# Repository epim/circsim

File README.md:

# circsim

**Simulate and audit any routed KiCad board.** circsim is a desktop app (Windows / macOS / Linux) that opens a routed KiCad board (`.kicad_pcb`), rebuilds the circuit from the copper, renders it in 3D, and runs an interactive SPICE bench on it: apply power, turn a knob, probe nets on the physical board. A read-only Board Critic audits the layout for fabrication risks. You get both before you pay for fabrication.

Open the board and press Energize. You do not assign `Sim.*` fields first, and the bundled model library matches parts by part number, value, and footprint, flagging the ones it cannot match instead of guessing. circsim is fully offline, MIT-licensed, and **never modifies your design files.**

Documentation: **[epim.github.io/circsim](https://epim.github.io/circsim/)**. It has the install guide, the First Light tutorial, task how-tos, and the full reference.
Download: **[latest release](https://github.com/epim/circsim/releases/latest)** (Windows `.exe`, macOS `.dmg` x2, Linux `.AppImage` / `.deb`).

More screenshots, and what circsim reads out of sixteen KiCad-written boards from KiCad 6 through 10, are in the [gallery](https://epim.github.io/circsim/gallery).

## What it does

- **Starts from the routed board.** Net connectivity comes straight out of the `.kicad_pcb`, KiCad 6 to 10. The board can come from your own KiCad project, a contractor, or an autorouter such as [Quilter](https://quilter.ai) that returns a KiCad board; circsim has no Quilter-specific code. The [supported files](https://epim.github.io/circsim/reference/file-formats#kicad-version-support) page lists the KiCad-written boards behind the version range, including the one it rejects.
- **The schematic is an optional input.** Keep the `.kicad_sch` next to the board with the same name and circsim attaches it on open. Its `Sim.*` fields are the first model source and its pin names settle diode and LED polarity. Only the root sheet is read, so parts on hierarchical sub-sheets get neither. A BOM CSV pins down exact parts.
- **A real bench.** Clip a DC supply, function generator, potentiometer, logic input, and voltage/current probes onto the board by drawing leads from front-panel jacks to the copper. Turn a knob and the simulation re-solves live.
- **A read-only Board Critic on the layout.** It audits the board circsim did *not* design for floating nets, clearance, decoupling distance, loop area, IR-drop, ampacity, and thermal risk, and never edits your files. The simulation itself treats each net as one ideal node, so copper resistance appears in the Critic's estimates and not in the simulated voltages.
- **Honest about what it knows.** Behavioral vs. primitive models, stubbed ICs, MCUs as interactive-pin panels (firmware doesn't run), convergence fallbacks, and fidelity limits are always visible. See [what circsim can and can't tell you](https://epim.github.io/circsim/concepts/fidelity). The same page ships inside the app.

Powered by [ngspice](https://ngspice.sourceforge.io/) 46, bundled per platform and run crash-isolated in a separate process. Nothing to install; no network calls, ever, and the app enforces it by cancelling any request that is not a local file.

## Develop

```sh
npm install
npm run fetch:ngspice   # download the bundled SPICE engine for your platform
npm run dev             # run the app in dev mode
npm test                # vitest unit + integration suite
npm run typecheck       # tsconfig.node.json + tsconfig.web.json (what CI runs)
npm run test:e2e        # Playwright E2E (requires npm run build first)
npm run build           # build the app
npm run package         # produce installers for the current platform
```

Architecture: Electron + TypeScript + React (panels) + imperative Three.js/WebGL2 (3D viewport) + zustand (state). The framework-free `src/core/` layer (KiCad parsing, netlist extraction, model resolution, SPICE-deck generation, the Board Critic) is fully unit-tested without Electron. See the [architecture reference](https://epim.github.io/circsim/reference/architecture).

## Documentation source

The docs site is a VitePress project under [`website/`](website/), deployed to GitHub Pages by [`.github/workflows/docs.yml`](.github/workflows/docs.yml) on every push touching `website/`. To work on it:

```sh
cd website && npm install && npm run docs:dev
```

The page the app opens from its About dialog and fidelity banner is rendered from `website/docs/concepts/fidelity.md`. After editing that page, run `npm run docs:fidelity` and commit the regenerated `docs/what-circsim-can-tell-you.html`; a unit test fails when the two drift.

## License

MIT. circsim bundles ngspice (BSD-style) and an in-house SPICE model library written from datasheet parameters; it never bundles vendor SPICE models or KiCad's share-alike 3D assets. See [`docs/licensing.md`](docs/licensing.md) and the in-app **About** dialog for full provenance.

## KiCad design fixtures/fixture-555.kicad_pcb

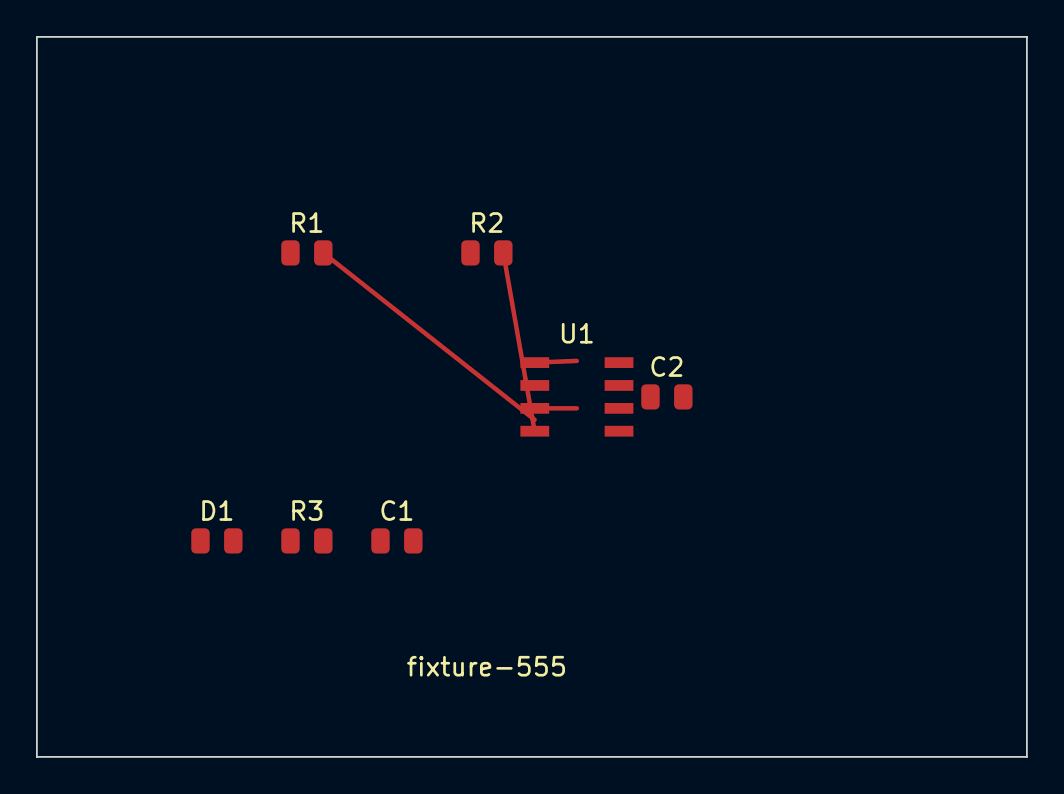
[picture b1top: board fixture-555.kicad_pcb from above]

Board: 2 copper layers, 55.0 x 40.0 mm, 7 parts (0 on the bottom side), 7 nets.

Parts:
C1: 10u; C_0805_2012Metric
C2: 100n; C_0805_2012Metric
D1: LED; LED_0805_2012Metric
R1: 10k; R_0805_2012Metric
R2: 47k; R_0805_2012Metric
R3: 330; R_0805_2012Metric
U1: NE555; SOIC-8_3.9x4.9mm_P1.27mm

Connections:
CTRL: C2.1, U1.5
DISCH: R1.2, R2.1, U1.7
GND: C1.2, C2.2, D1.2, U1.1
LED_A: D1.1, R3.2
OUT: R3.1, U1.3
THRES: C1.1, R2.2, U1.2, U1.6
VCC: R1.1, U1.4, U1.8

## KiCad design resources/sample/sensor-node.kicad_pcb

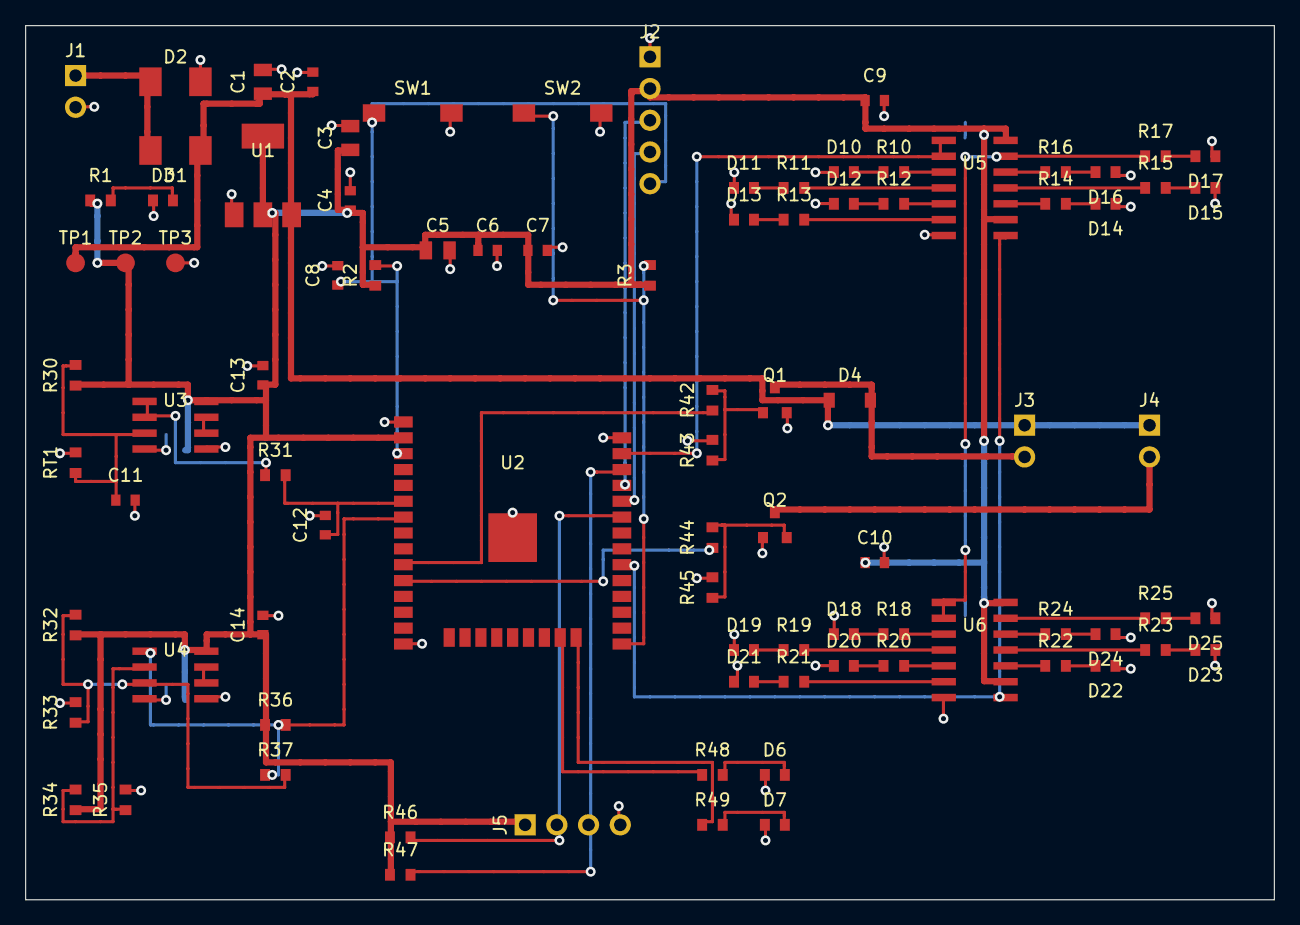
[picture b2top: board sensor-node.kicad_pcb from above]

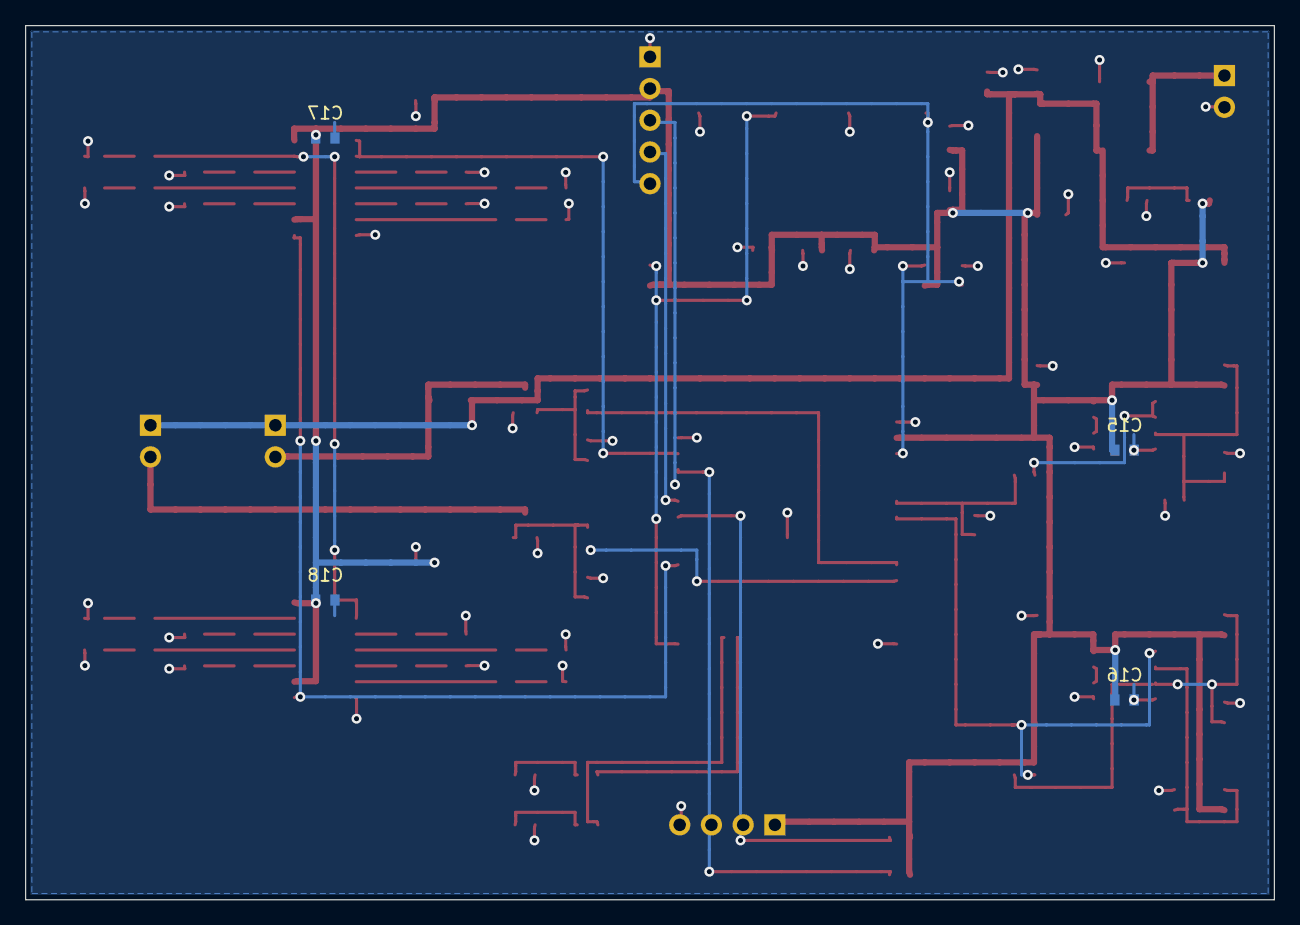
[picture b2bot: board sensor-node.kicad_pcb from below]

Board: 2 copper layers, 100.0 x 70.0 mm, 94 parts (4 on the bottom side), 63 nets.

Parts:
C1, C5: 10u; C_0805_2012Metric
C2, C4, C6, C7, C9, C10, C11, C13, C14, C15, C16, C17, C18: 100n; C_0603_1608Metric
C3: 22u; C_0805_2012Metric
C8: 1u; C_0603_1608Metric
C12: 10n; C_0603_1608Metric
D1: SS14; D_SMA
D2: SMAJ24A; D_SMA
D3, D6, D7, D10, D11, D12, D13, D14, D15, D16, D17, D18, D19, D20, D21, D22, D23, D24, D25: LED; LED_0603_1608Metric
D4: 1N4148W; D_SOD-123
J1, J3, J4: Conn_01x02; PinHeader_1x02_P2.54mm_Vertical
J2: Conn_01x05; PinHeader_1x05_P2.54mm_Vertical
J5: Conn_01x04; PinHeader_1x04_P2.54mm_Vertical
Q1: 2N7002; SOT-23
Q2: 2N3904; SOT-23
R1, R10, R11, R12, R13, R14, R15, R16, R17, R18, R19, R20, R21, R22, R23, R24, R25: 330; R_0603_1608Metric
R2, R3, R30, R32, R33, R36, R45: 10k; R_0603_1608Metric
R31, R44, R48, R49: 1k; R_0603_1608Metric
R34, R35: 47k; R_0603_1608Metric
R37: 1M; R_0603_1608Metric
R42: 220; R_0603_1608Metric
R43: 100k; R_0603_1608Metric
R46, R47: 4.7k; R_0603_1608Metric
RT1: 10k; R_0603_1608Metric
SW1, SW2: SW_Push; SW_SPST_PTS645
TP1, TP2, TP3: TestPoint; TestPoint_Pad_D1.5mm
U1: AMS1117-3.3; SOT-223
U2: ESP32-WROOM-32
U3: LM358; SOIC-8_3.9x4.9mm_P1.27mm
U4: LM393; SOIC-8_3.9x4.9mm_P1.27mm
U5, U6: 74HC164; SOIC-14_3.9x8.7mm_P1.27mm

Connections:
+3V3: C3.1, C4.1, C5.1, C6.1, C7.1, C9.1, C10.1, C13.1, C14.1, C15.1, C16.1, C17.1, C18.1, J2.2, J5.1, R1.1, R2.1, R3.1, R30.1, R32.1, R34.1, R36.1, R46.1, R47.1, TP2.1, U1.2, U1.4, U2.2, U3.8, U4.8, U5.9, U5.14, U6.9, U6.14
+5V: C1.1, C2.1, D1.1, D4.1, J3.1, J4.1, TP1.1, U1.3
EN: C8.1, J2.5, R2.2, SW1.1, U2.3
FAN_G: Q1.1, R42.2, R43.1
FAN_G_IN: R42.1, U2.10
FAN_NEG: D4.2, J3.2, Q1.3
GND: C1.2, C2.2, C3.2, C4.2, C5.2, C6.2, C7.2, C8.2, C9.2, C10.2, C11.2, C12.2, C13.2, C14.2, C15.2, C16.2, C17.2, C18.2, D2.2, D3.1, D6.1, D7.1, D10.1, D11.1, D12.1, D13.1, D14.1, D15.1, D16.1, D17.1, D18.1, D19.1, D20.1, D21.1, D22.1, D23.1, D24.1, D25.1, J1.2, J2.1, J5.4, Q1.2, Q2.1, R33.2, R35.2, R43.2, R45.2, RT1.2, SW1.2, SW2.2, TP3.1, U1.1, U2.1, U2.15, U2.38, U2.39, U3.4, U3.5, U4.4, U4.5, U5.7, U6.7
IO0: R3.2, SW2.1, U2.25
LA1: D10.2, R10.1
LA2: D11.2, R11.1
LA3: D12.2, R12.1
LA4: D13.2, R13.1
LA5: D14.2, R14.2
LA6: D15.2, R15.2
LA7: D16.2, R16.2
LA8: D17.2, R17.2
LA9: D18.2, R18.1
LA10: D19.2, R19.1
LA11: D20.2, R20.1
LA12: D21.2, R21.1
LA13: D22.2, R22.2
LA14: D23.2, R23.2
LA15: D24.2, R24.2
LA16: D25.2, R25.2
LDR_SENSE: R32.2, R33.1, R37.2, U4.3
LED_STATUS1: R48.1, U2.23
LED_STATUS2: R49.1, U2.24
LIGHT_ADC: R36.2, R37.1, U2.7, U4.1
LIGHT_REF: R34.2, R35.1, U4.2
NTC_SENSE: C11.1, R30.2, RT1.1, U3.3
PWR_LED_A: D3.2, R1.2
Q1: R10.2, U5.3
Q2: R11.2, U5.4
Q3: R12.2, U5.5
Q4: R13.2, U5.6
Q5: R14.1, U5.10
Q6: R15.1, U5.11
Q7: R16.1, U5.12
Q8: R17.1, U5.13, U6.1, U6.2
Q9: R18.2, U6.3
Q10: R19.2, U6.4
Q11: R20.2, U6.5
Q12: R21.2, U6.6
Q13: R22.1, U6.10
Q14: R23.1, U6.11
Q15: R24.1, U6.12
Q16: R25.1, U6.13
RXD: J2.4, U2.34
S1_A: D6.2, R48.2
S2_A: D7.2, R49.2
SCL: J5.3, R47.2, U2.36
SDA: J5.2, R46.2, U2.33
SR_CLK: U2.30, U5.8, U6.8
SR_DATA: U2.37, U5.1, U5.2
STRIP_B: Q2.2, R44.2, R45.1
STRIP_G_IN: R44.1, U2.11
STRIP_NEG: J4.2, Q2.3
TEMP_ADC: C12.1, R31.2, U2.6
TEMP_OUT: R31.1, U3.1, U3.2
TXD: J2.3, U2.35
U3_NC: U3.6, U3.7
U4_NC: U4.6, U4.7
VIN_RAW: D1.2, D2.1, J1.1

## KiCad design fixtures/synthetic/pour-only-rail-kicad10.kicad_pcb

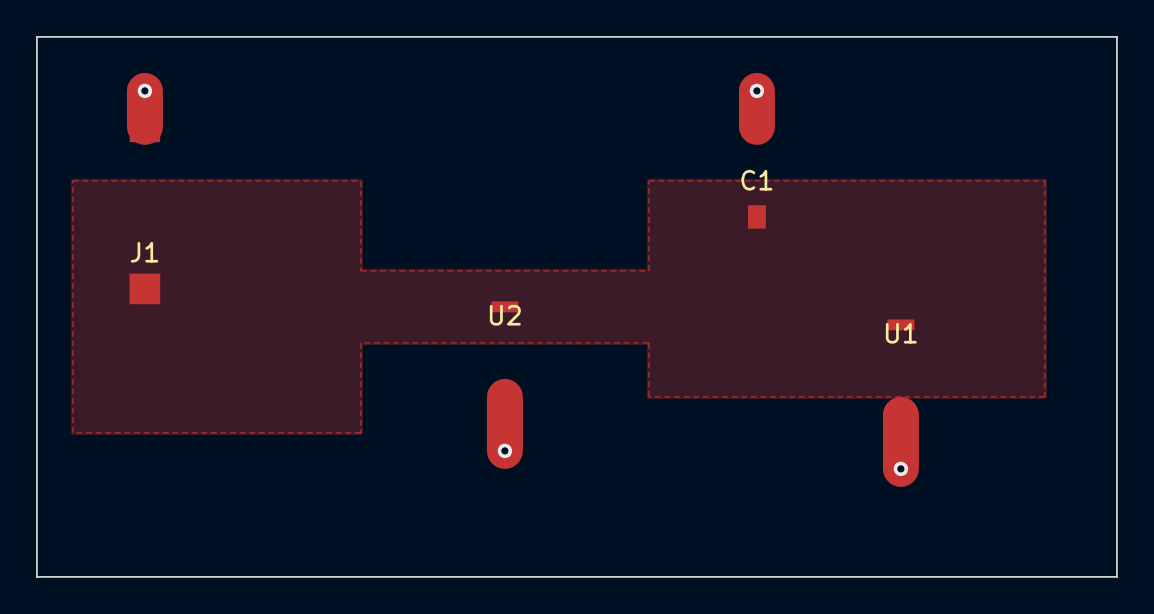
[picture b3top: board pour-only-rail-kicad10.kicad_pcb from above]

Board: 2 copper layers, 60.0 x 30.0 mm, 4 parts (0 on the bottom side), 2 nets.

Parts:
C1: 100n; C_0805_2012Metric
J1: Conn_01x02; PinHeader_1x02_P2.54mm_Vertical
U1, U2: LM358; SOIC-8_3.9x4.9mm_P1.27mm

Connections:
GND: C1.2, J1.2, U1.4, U2.4
VCC: C1.1, J1.1, U1.8, U2.8

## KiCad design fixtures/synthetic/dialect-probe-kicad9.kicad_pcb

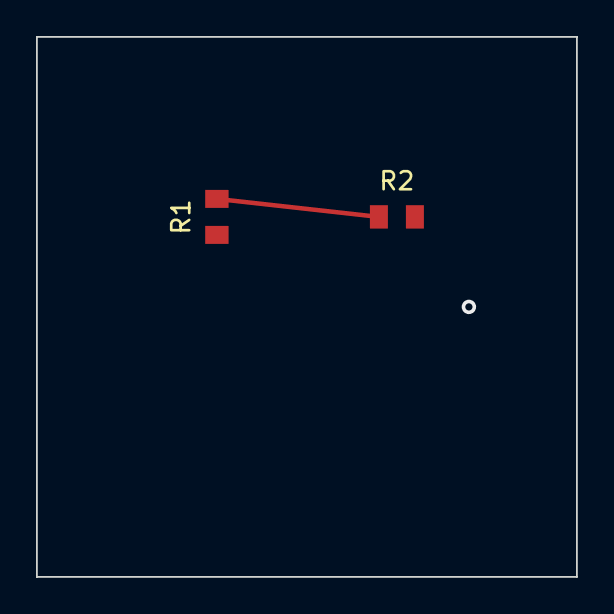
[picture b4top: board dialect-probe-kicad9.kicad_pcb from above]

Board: 2 copper layers, 30.0 x 30.0 mm, 3 parts (1 on the bottom side), 2 nets.

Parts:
C1: 100n; C_0805_2012Metric
R1, R2: 10k; R_0805_2012Metric

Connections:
GND: C1.2, R2.2
MID: C1.1, R1.2, R2.1

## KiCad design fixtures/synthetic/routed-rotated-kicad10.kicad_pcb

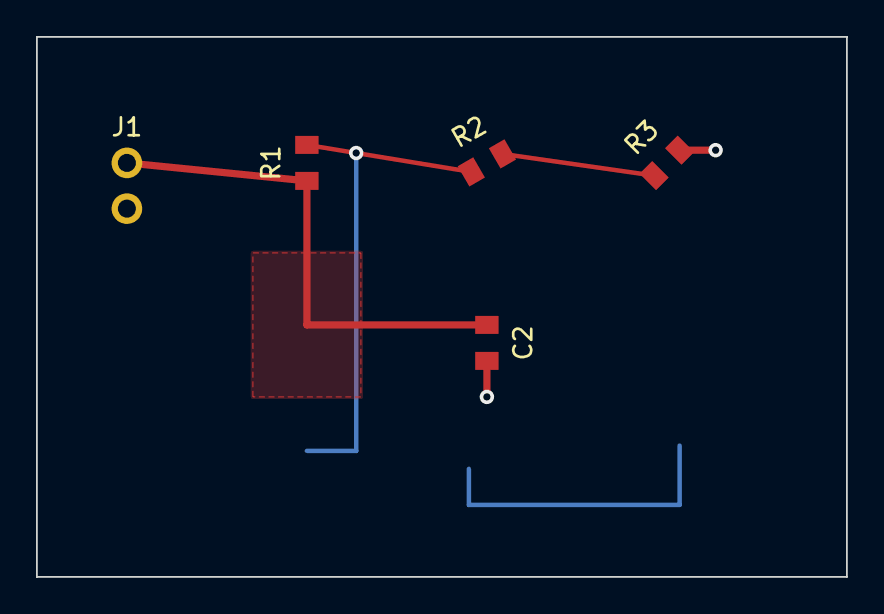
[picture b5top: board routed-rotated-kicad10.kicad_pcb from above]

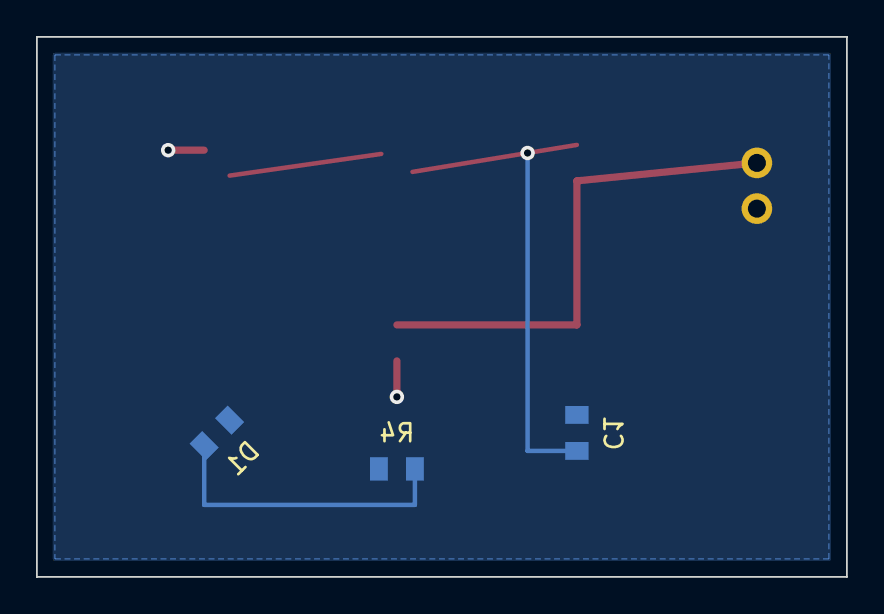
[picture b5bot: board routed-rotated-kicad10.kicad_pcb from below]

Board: 2 copper layers, 45.0 x 30.0 mm, 8 parts (3 on the bottom side), 5 nets.

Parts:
C1, C2: 100n; C_0805_2012Metric
D1: LED; LED_0805_2012Metric
J1: Conn_01x02; PinHeader_1x02_P2.54mm_Vertical
R1: 10k; R_0805_2012Metric
R2: 4.7k; R_0805_2012Metric
R3: 1k; R_0805_2012Metric
R4: 2.2k; R_0805_2012Metric

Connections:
GND: C1.2, C2.2, D1.2, J1.2, R3.2, R4.2
N1: C1.1, R1.2, R2.1
N2: R2.2, R3.1
SIG: D1.1, R4.1
VIN: C2.1, J1.1, R1.1

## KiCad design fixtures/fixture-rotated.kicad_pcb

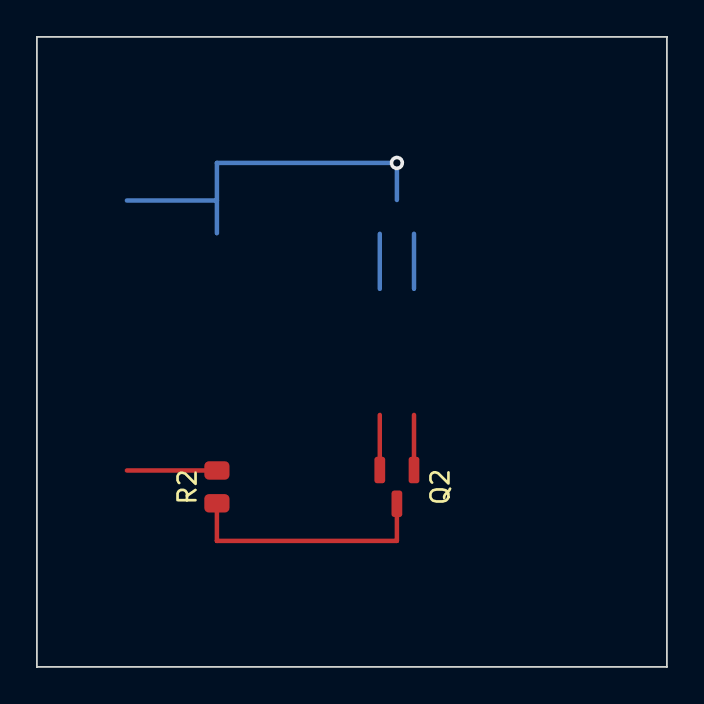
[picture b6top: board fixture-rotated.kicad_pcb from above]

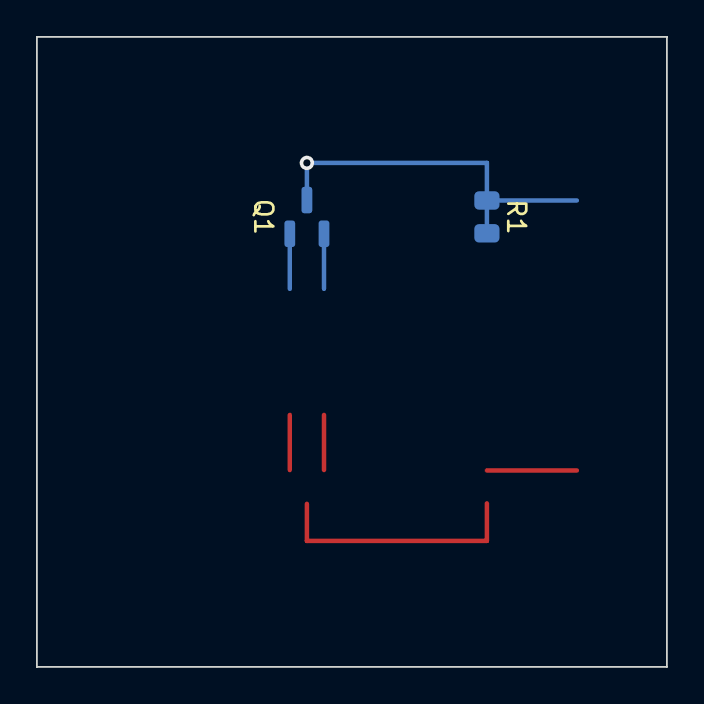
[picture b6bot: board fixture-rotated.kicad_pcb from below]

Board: 2 copper layers, 35.0 x 35.0 mm, 4 parts (2 on the bottom side), 3 nets.

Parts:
Q1, Q2: BSS138; SOT-23
R1: 10k; R_0805_2012Metric
R2: 1k; R_0805_2012Metric

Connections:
GND: Q1.2, Q2.2, R2.2
MID: Q1.3, Q2.3, R1.2, R2.1
SIG: Q1.1, Q2.1
